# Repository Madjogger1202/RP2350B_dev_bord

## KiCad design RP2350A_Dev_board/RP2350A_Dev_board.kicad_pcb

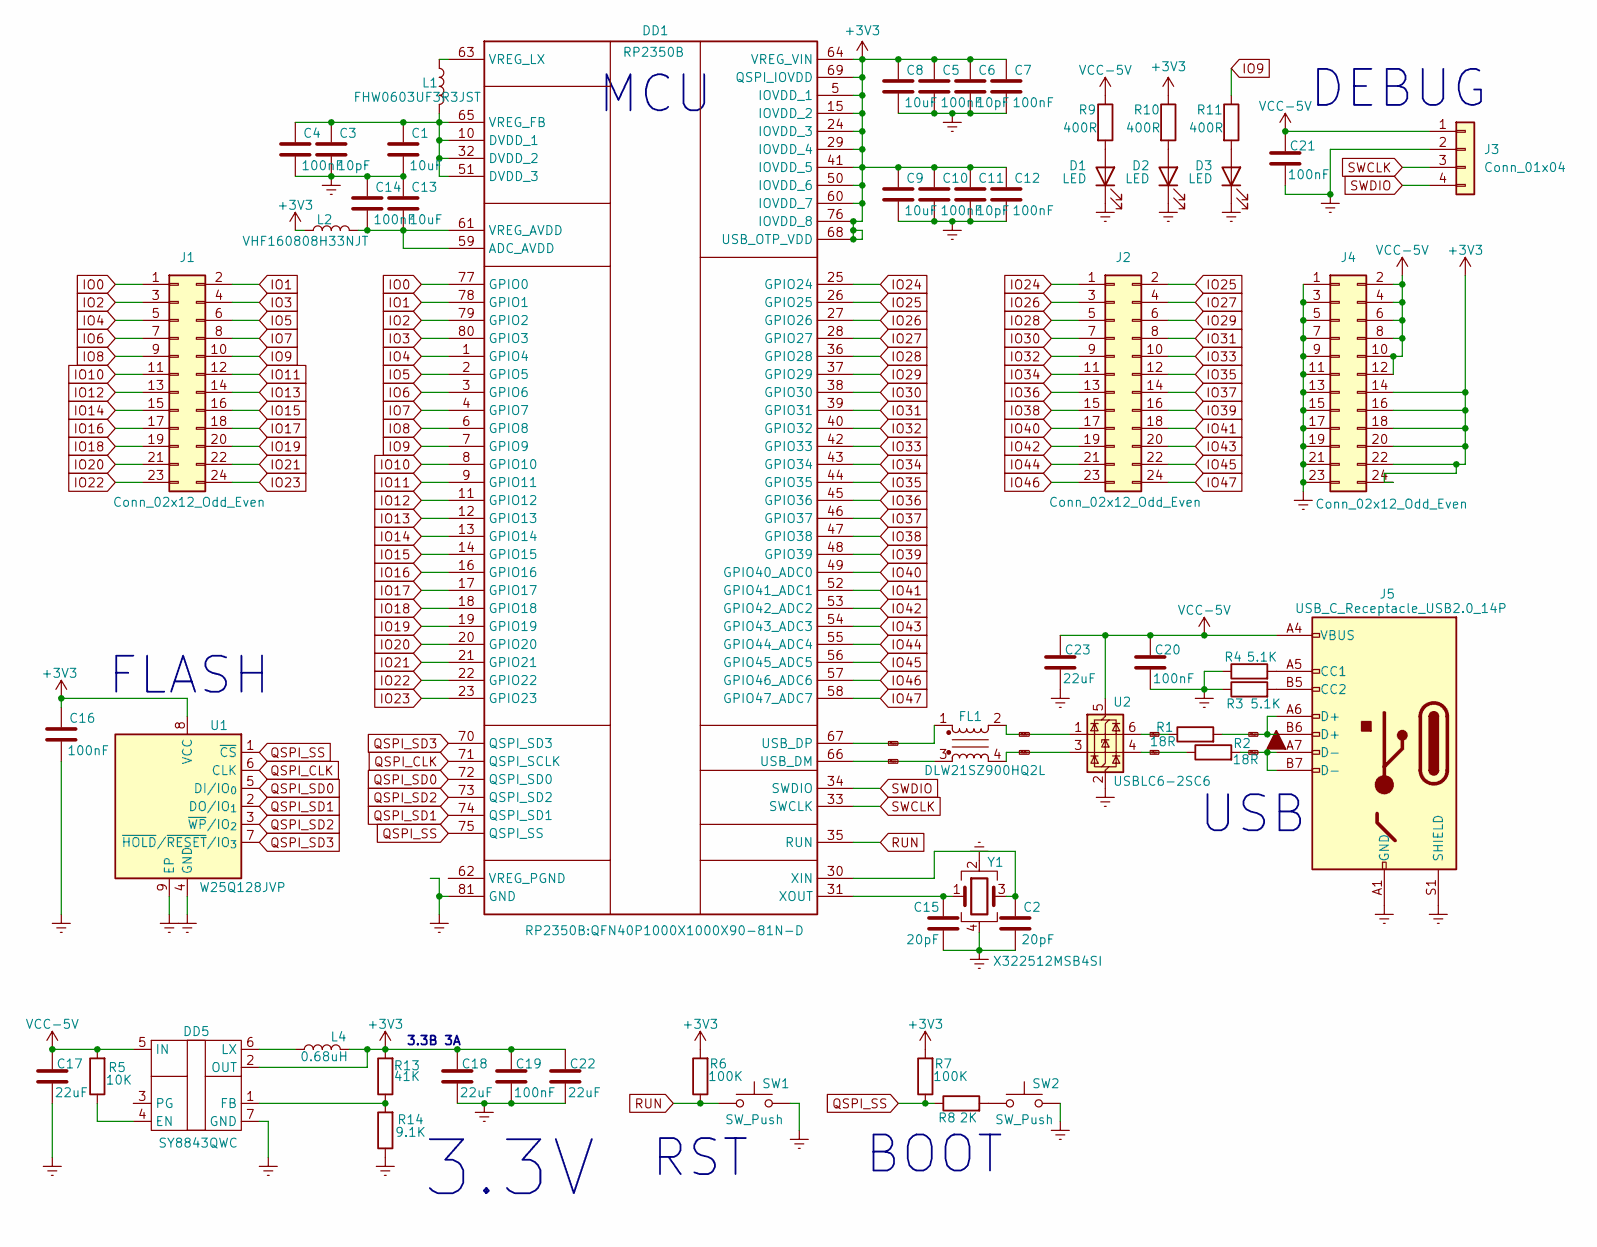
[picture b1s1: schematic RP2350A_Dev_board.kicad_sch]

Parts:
C1, C8, C9, C13: 10uF; C_0603_1608Metric
C2, C15: 20pF; C_0603_1608Metric
C3, C6, C11: 10pF; C_0603_1608Metric
C4, C5, C7, C10, C12, C14, C16: 100nF; C_0603_1608Metric
C17, C18, C22, C23: 22uF; C_0402_1005Metric
C19, C20, C21: 100nF; C_0402_1005Metric
D1, D2, D3: LED; LED_0603_1608Metric
DD1: RP2350B; QFN40P1000X1000X90-81N-D; Manufacturer_Part_Number RP2350B
DD5: SY8843QWC
FL1: DLW21SZ900HQ2L; L_CommonModeChoke_Coilcraft_0805USB
J1, J2, J4: Conn_02x12_Odd_Even; Hirose_DF11-24DP-2DSA_2x12_P2.00mm_Vertical
J3: Conn_01x04; Molex_KK-254_AE-6410-04A_1x04_P2.54mm_Vertical
J5: USB_C_Receptacle_USB2.0_14P; USB_C_Receptacle_GCT_USB4105-xx-A_16P_TopMnt_Horizontal
L1: FHW0603UF3R3JST; L_0603_1608Metric
L2: VHF160808H33NJT; L_0603_1608Metric
L4: 0.68uH; L_Cenker_CKCS4020
R1, R2: 18R; R_01005_0402Metric
R3, R4: 5.1K; R_01005_0402Metric
R5: 10K; R_0402_1005Metric
R6, R7: 100K; R_01005_0402Metric
R8: 2K; R_01005_0402Metric
R9, R10, R11: 400R; R_01005_0402Metric
R13: 41К; R_0402_1005Metric
R14: 9.1K; R_0402_1005Metric
SW1, SW2: SW_Push; SW_SPST_PTS810
U1: W25Q128JVP; WSON-8-1EP_6x5mm_P1.27mm_EP3.4x4.3mm
U2: USBLC6-2SC6; SOT-23-6
Y1: X322512MSB4SI; Crystal_SMD_3225-4Pin_3.2x2.5mm

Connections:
+3V3: C5.2, C6.2, C7.2, C8.2, C9.2, C10.2, C11.2, C12.2, C16.2, C18.1, C19.1, C22.1, DD1.5 (IOVDD_1), DD1.15 (IOVDD_2), DD1.24 (IOVDD_3), DD1.29 (IOVDD_4), DD1.41 (IOVDD_5), DD1.50 (IOVDD_6), DD1.60 (IOVDD_7), DD1.64 (VREG_VIN), DD1.68 (USB_OTP_VDD), DD1.69 (QSPI_IOVDD), DD1.76 (IOVDD_8), DD5.2 (OUT), J4.14, J4.16, J4.18, J4.20, J4.22, J4.24, L2.1, L4.2, R6.2, R7.2, R10.1, R13.2, U1.8 (VCC)
Earth: C1.1, C2.1, C3.1, C4.1, C5.1, C6.1, C7.1, C8.1, C9.1, C10.1, C11.1, C12.1, C13.2, C14.2, C15.1, C16.1, C17.2, C18.2, C19.2, C20.2, C21.2, C22.2, C23.2, D1.1 (K), D2.1 (K), D3.1 (K), DD1.62 (VREG_PGND), DD1.81 (GND), DD5.7 (GND), J3.2, J4.1, J4.3, J4.5, J4.7, J4.9, J4.11, J4.13, J4.15, J4.17, J4.19, J4.21, J4.23, J5.A1 (GND), J5.A12 (GND), J5.B1 (GND), J5.B12 (GND), J5.S1 (SHIELD), R3.1, R4.1, R14.1, SW1.2, SW2.2, U1.4 (GND), U1.9 (EP), U2.2 (GND), Y1.2, Y1.4
IO0: DD1.77 (GPIO0), J1.1
IO1: DD1.78 (GPIO1), J1.2
IO2: DD1.79 (GPIO2), J1.3
IO3: DD1.80 (GPIO3), J1.4
IO4: DD1.1 (GPIO4), J1.5
IO5: DD1.2 (GPIO5), J1.6
IO6: DD1.3 (GPIO6), J1.7
IO7: DD1.4 (GPIO7), J1.8
IO8: DD1.6 (GPIO8), J1.9
IO9: DD1.7 (GPIO9), J1.10, R11.1
IO10: DD1.8 (GPIO10), J1.11
IO11: DD1.9 (GPIO11), J1.12
IO12: DD1.11 (GPIO12), J1.13
IO13: DD1.12 (GPIO13), J1.14
IO14: DD1.13 (GPIO14), J1.15
IO15: DD1.14 (GPIO15), J1.16
IO16: DD1.16 (GPIO16), J1.17
IO17: DD1.17 (GPIO17), J1.18
IO18: DD1.18 (GPIO18), J1.19
IO19: DD1.19 (GPIO19), J1.20
IO20: DD1.20 (GPIO20), J1.21
IO21: DD1.21 (GPIO21), J1.22
IO22: DD1.22 (GPIO22), J1.23
IO23: DD1.23 (GPIO23), J1.24
IO24: DD1.25 (GPIO24), J2.1
IO25: DD1.26 (GPIO25), J2.2
IO26: DD1.27 (GPIO26), J2.3
IO27: DD1.28 (GPIO27), J2.4
IO28: DD1.36 (GPIO28), J2.5
IO29: DD1.37 (GPIO29), J2.6
IO30: DD1.38 (GPIO30), J2.7
IO31: DD1.39 (GPIO31), J2.8
IO32: DD1.40 (GPIO32), J2.9
IO33: DD1.42 (GPIO33), J2.10
IO34: DD1.43 (GPIO34), J2.11
IO35: DD1.44 (GPIO35), J2.12
IO36: DD1.45 (GPIO36), J2.13
IO37: DD1.46 (GPIO37), J2.14
IO38: DD1.47 (GPIO38), J2.15
IO39: DD1.48 (GPIO39), J2.16
IO40: DD1.49 (GPIO40_ADC0), J2.17
IO41: DD1.52 (GPIO41_ADC1), J2.18
IO42: DD1.53 (GPIO42_ADC2), J2.19
IO43: DD1.54 (GPIO43_ADC3), J2.20
IO44: DD1.55 (GPIO44_ADC4), J2.21
IO45: DD1.56 (GPIO45_ADC5), J2.22
IO46: DD1.57 (GPIO46_ADC6), J2.23
IO47: DD1.58 (GPIO47_ADC7), J2.24
unnamed: D1.2 (A), R9.2
unnamed: D2.2 (A), R10.2
unnamed: D3.2 (A), R11.2
unnamed: C13.1, C14.1, DD1.59 (ADC_AVDD), DD1.61 (VREG_AVDD), L2.2
unnamed: C1.2, C3.2, C4.2, DD1.10 (DVDD_1), DD1.32 (DVDD_2), DD1.51 (DVDD_3), DD1.65 (VREG_FB), L1.2
unnamed: DD1.63 (VREG_LX), L1.1
unnamed: C2.2, DD1.30 (XIN), Y1.3
unnamed: C15.2, DD1.31 (XOUT), Y1.1
unnamed: DD5.4 (EN), R5.1
unnamed: DD5.1 (FB), R13.1, R14.2
unnamed: DD5.6 (LX), L4.1
unnamed: J5.A5 (CC1), R4.2
unnamed: J5.B5 (CC2), R3.2
unnamed: R8.2, SW2.1
QSPI_CLK: DD1.71 (QSPI_SCLK), U1.6 (CLK)
QSPI_SD0: DD1.72 (QSPI_SD0), U1.5 (DI/IO_{0})
QSPI_SD1: DD1.74 (QSPI_SD1), U1.2 (DO/IO_{1})
QSPI_SD2: DD1.73 (QSPI_SD2), U1.3 (~WP/IO_{2})
QSPI_SD3: DD1.70 (QSPI_SD3), U1.7 (~HOLD/~RESET/IO_{3})
QSPI_SS: DD1.75 (QSPI_SS), R7.1, R8.1, U1.1 (~CS)
RUN: DD1.35 (RUN), R6.1, SW1.1
SWCLK: DD1.33 (SWCLK), J3.3
SWDIO: DD1.34 (SWDIO), J3.4
USB_con+: J5.A6 (D+), J5.B6 (D+), R1.2
USB_con-: J5.A7 (D-), J5.B7 (D-), R2.2
USB_filter+: FL1.2, U2.1 (I/O1)
USB_filter-: FL1.4, U2.3 (I/O2)
USB_mcu+: DD1.67 (USB_DP), FL1.1
USB_mcu-: DD1.66 (USB_DM), FL1.3
USB_res+: R1.1, U2.6 (I/O1)
USB_res-: R2.1, U2.4 (I/O2)
VCC-5V: C17.1, C20.1, C21.1, C23.1, DD5.5 (IN), J3.1, J4.2, J4.4, J4.6, J4.8, J4.10, J4.12, J5.A4 (VBUS), J5.A9 (VBUS), J5.B4 (VBUS), J5.B9 (VBUS), R5.2, R9.1, U2.5 (VBUS)

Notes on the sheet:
MCU
BOOT
RST
USB
FLASH
DEBUG
3.3V
3.3В 3А

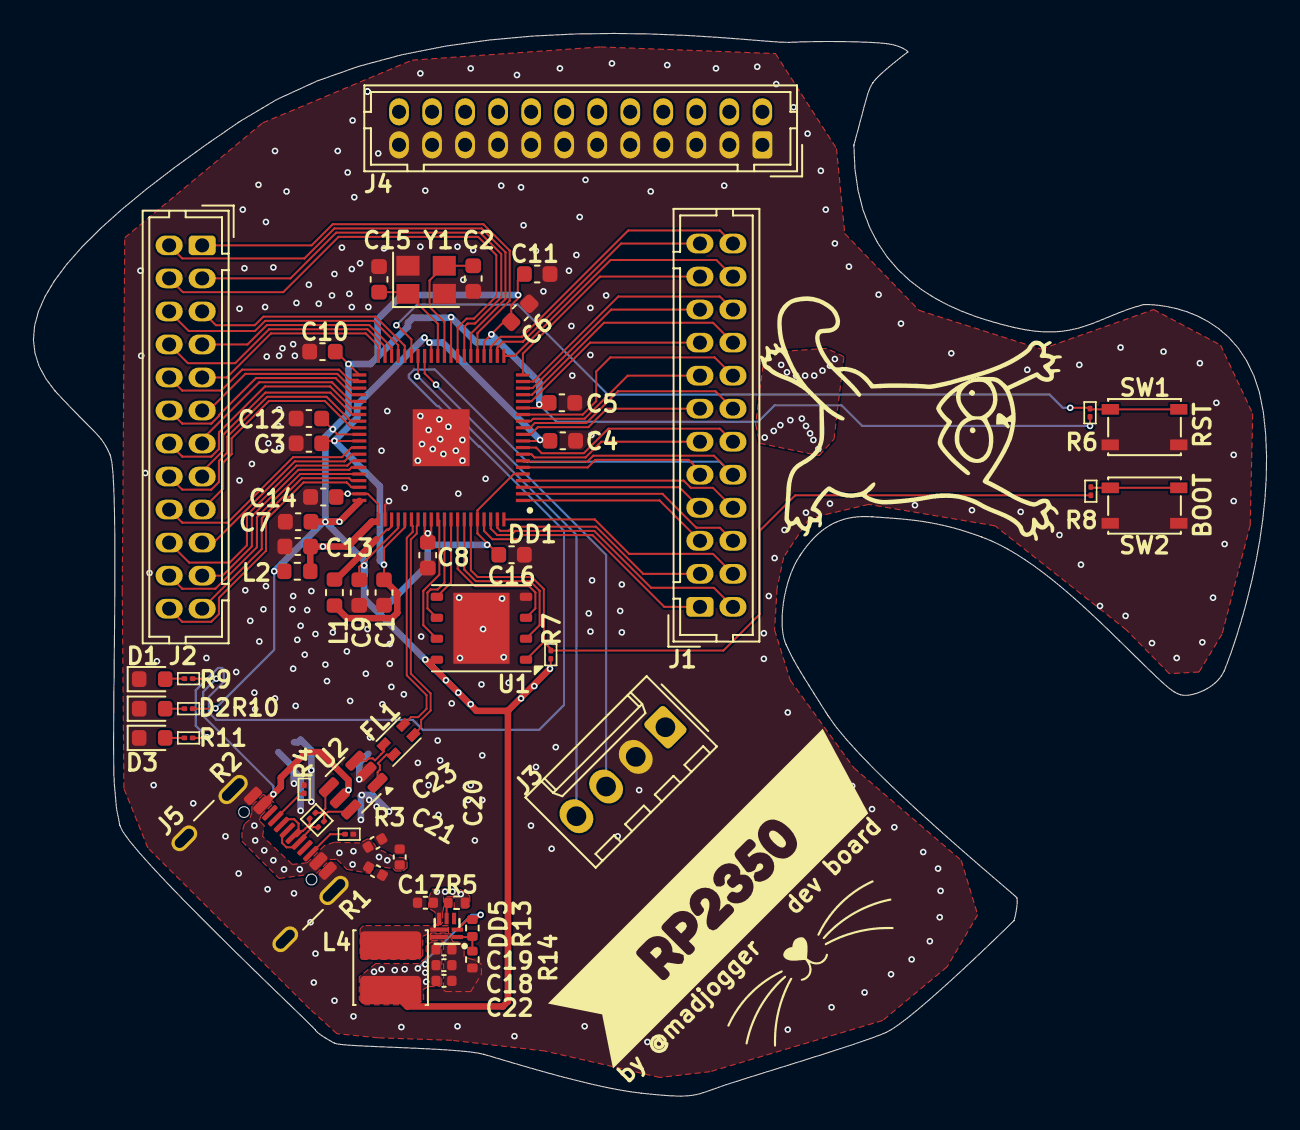
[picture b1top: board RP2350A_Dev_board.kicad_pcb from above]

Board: 2 copper layers, 74.7 x 64.3 mm, 56 parts (0 on the bottom side), 82 nets.

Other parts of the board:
kibuzzard-67ED7B45: G***; kibuzzard-67ED7B45

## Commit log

2025-04-01 Создал сам контроллер + обвязка основная уже присутствует Сформировал границы платы в соответствии с картинкой от нейронки
2025-04-02 почти всё, осталось только шелкографию сделать и готово
2025-04-02 Закончил :)
2025-04-03 Исправил сдвиг внутреннего соединения USB линии
2025-08-18 Update for DFM checking and manufacturing
